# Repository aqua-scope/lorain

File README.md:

<h1> Lora Rain Sensor </h1>

<p>Lorain is an affordable LoraWAN rain sensor utilizing the RAK 3172 Lora Module that can be programmed using Arduino environment. </p>

<h2> Hardware</h2>

<p>There are multiple ways to acquire the hardware for the LoRain. The Aqua-Scope Webshop at <a href="https://shop.aqua-scope.com">shop.aqua-scope.com</a> offers different options depending on your willingness to spent own effort in exchange for money:
<ul>
<li>Complete product tested and ready to use</li>
<li>Kit with all needed components and need to solder some of the components and flash the firmware. 
The kit includes a PCBA almost fully populated</li>
<li>The plain enclosure of the device. You need to order the PCB / <a href="img/lorain_pcba.jpg">PCBA</a>, purchase and solder all components and flash the firmware. The 'How-To' below assumes this option.</li>
</ul>
<p> The folder /hardware contains the gerber data and Bill of material of the PCBs. You can order the PCB from one of the usual suspects for fast and cheap PCB manufacturing like jlcpcb or pcbway. Ordering own PCB and soldering all components requires a certain level of hardware knowledge and soldering skills. Hence, we don’t provide additional guidance beside offering the files for the PCB.
</p>

<h2>How to complete the LoRain Kit</h2>

<p>The LoRain Kit consists of the following components (see <a href="img/lorain_kit.png">image</a>):
<ul>
<li>enclosure including screws for mounting the enclosure to a flat surface, PCBA compartment and battery compartment</li>
<li>one screw to hold the battery compartment</li>
<li>2 * AA Batteries</li>
<li>CBA SMD complete</li>
<li>1 * 8.6 mm whip antenna</li>
<li>2 * wires to connect PCBA with battery compartment</li>
<li>Button</li>
<li>Reed contact</li>
</uL>
<p>The PCBA needs some soldering as shown in this (<a href="img/lorain_pcb_solder.png">image</a>). Please note that all soldering are done on the B-Sie that does not have any components. No soldering needed on A side with the components.
</p>
<ul>
<li>Connect the Battery + contact if the PCBA to the battery + contact of the battery compartment using the red wires</li>
<li>Connect the Battery - contact if the PCBA to the battery contact of the battery compartment using the black wires (<a href="img/lorain_pcb_solder.png">image</a>)</li>
<li>Insert the button into the hole of the PCB and solder it on the four pins</li>
<li>Solder the reed contact on the B-side as shown on the silk screen (<a href="img/lorain_pcb_back.png">image</a>)</li>
<li>Solder the whip antenna to the antenna tru-hole</li>
</ul> 

<h2> Firmware </h2>
  
<p>The firmware is written as Arduino Sketch using the RAK Wireless Arduino Environment. You need to install the Arduino IDE and follow the instructions of <a href="https://docs.rakwireless.com/Product-Categories/WisDuo/RAK3172-Module/Quickstart/#rak3172-as-a-stand-alone-device-using-rui3"> RAK wireless </a> to install the RAK board support package. </p>
  
<p>To flash a new firmware you need a simple USB-TTL-UART connector (<a href="https://www.amazon.de/AZDelivery-Konverter-kompatibel-Arduino-inklusive/dp/B089QJZ51Z/ref=asc_df_B089QJZ51Z"> e.g. this </a>). The firmware update mode on the RAK module is enabled using the AT command 'AT+BOOT' on the serial console of the Arduino IDE. </p>

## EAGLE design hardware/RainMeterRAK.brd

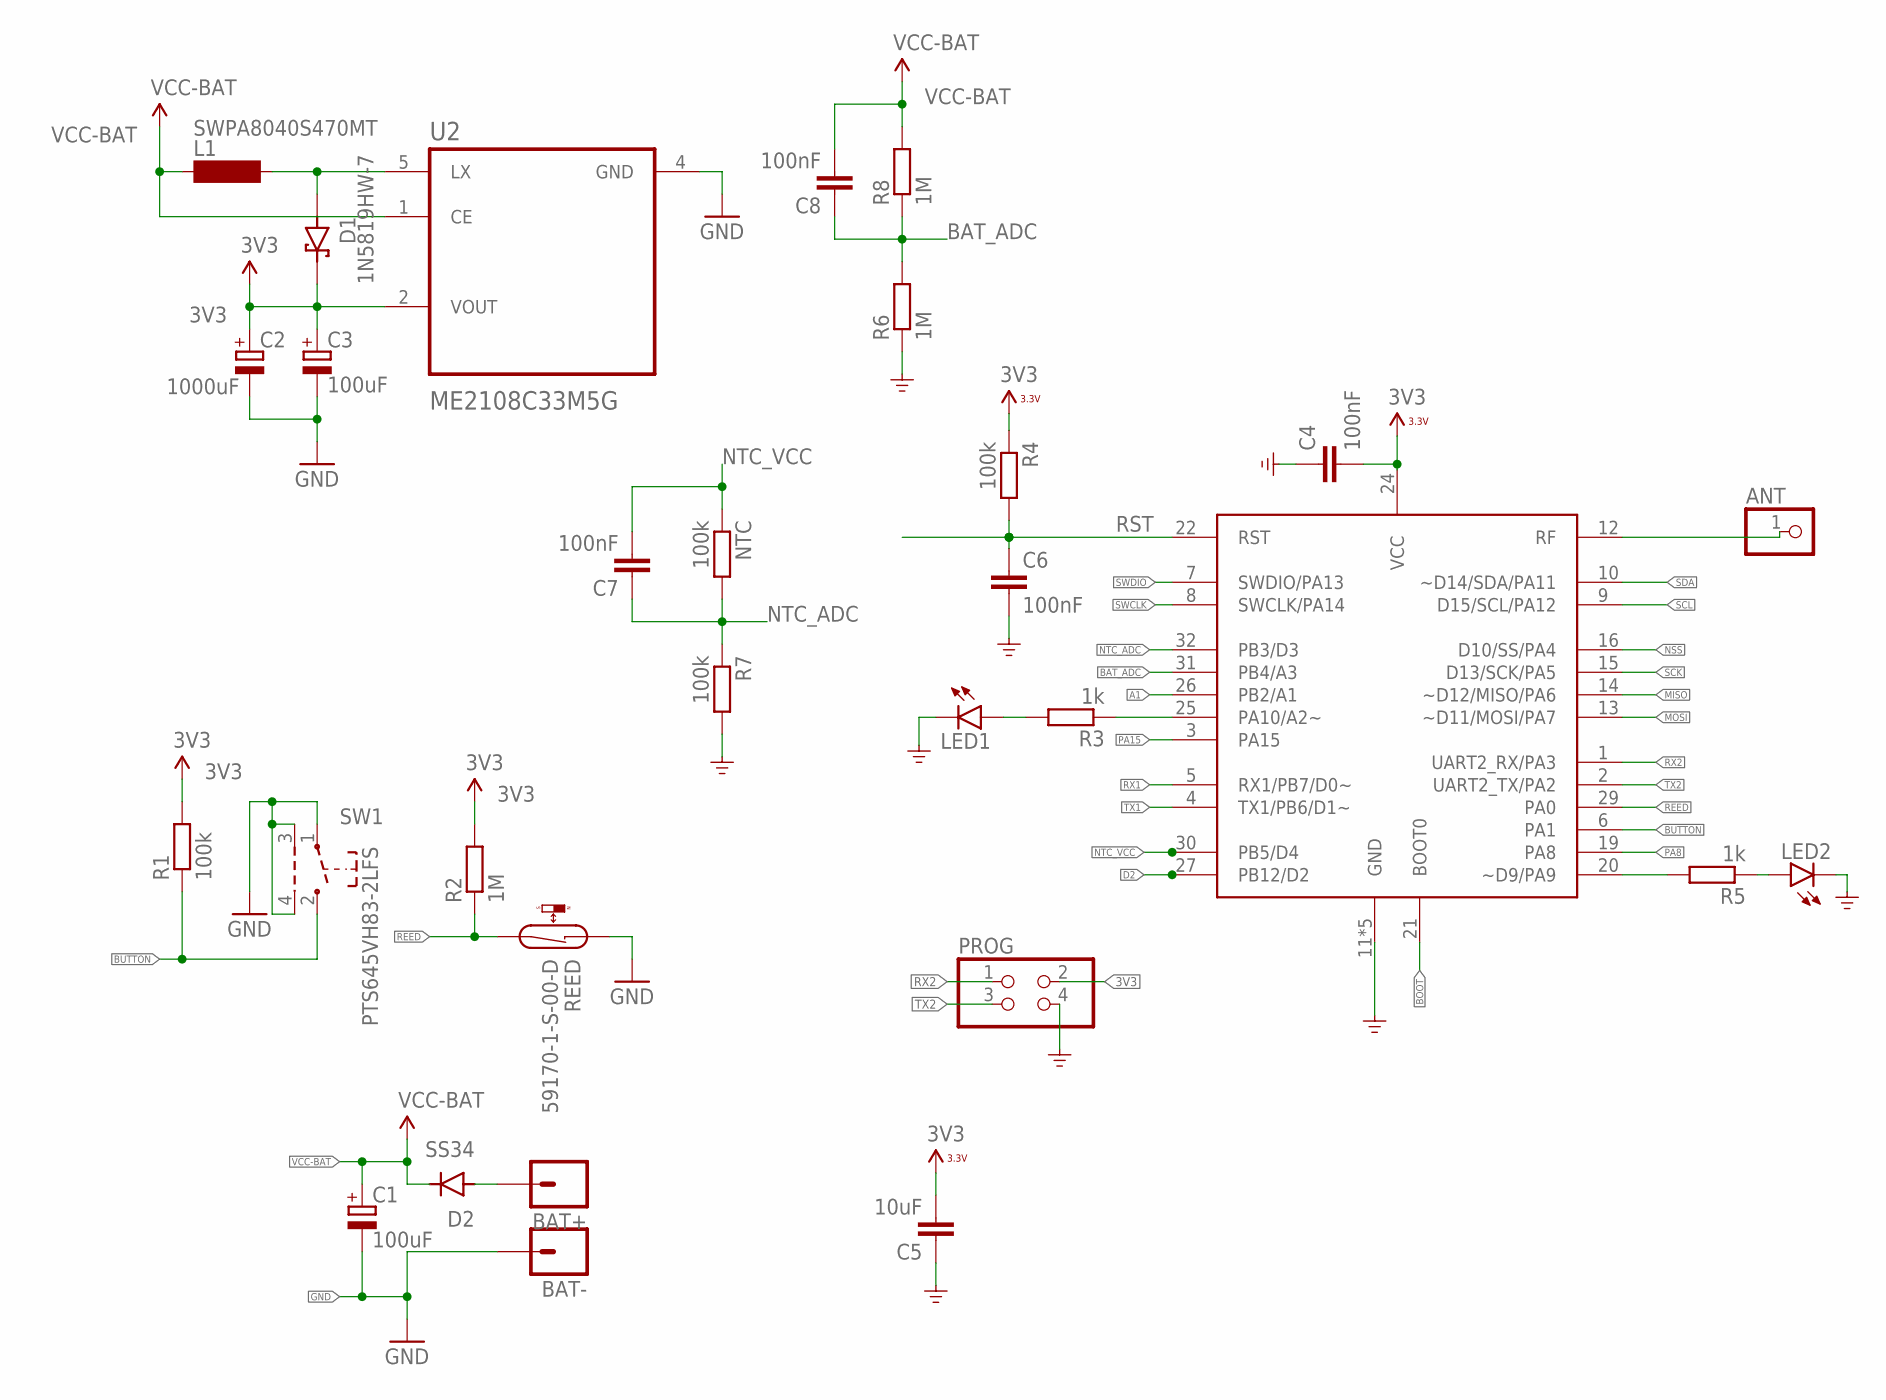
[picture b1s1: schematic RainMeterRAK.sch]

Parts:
ANT: PINHD-1X1; 1X01
BAT+: M01OFFSET; 1X01_OFFSET
BAT-: M01OFFSET; 1X01_OFFSET
C1, C3: 100uF; CT3528
C2: 1000uF; 140CLH-0810
C4, C6, C7, C8: 100nF; C0603
C5: 10uF; C0603
D1: 1N5819HW-7; SOD3715X145N
D2: SS34; SOD-123_MINI-SMA
L1: SWPA8040S470MT; SWPA8040S
LED1, LED2: LEDCHIP-LED0603; CHIP-LED0603
NTC: 100k; R0603
PROG: PINHD-2X2; 2X02
R1, R4, R7: 100k; R0603
R2, R6, R8: 1M; R0603
R3, R5: 1k; R0603
REED: 59170-1-S-00-D; CT10-G1
SW1: PTS645VH83-2LFS; SW_TACT_STANDARD_RIGHT_ANGLE
U1: RAK3172HF; RAK3172
U2: ME2108C33M5G; SOT23-5

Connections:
3V3: C2.+, C3.+, C4.2, C5.2, D1.C (K), PROG.2, R1.2, R2.2, R4.1, U1.24 (VCC), U2.2 (VOUT)
A1: U1.26 (PB2/A1)
BAT_ADC: C8.1, R6.2, R8.1, U1.31 (PB4/A3)
BOOT: U1.21 (BOOT0)
BUTTON: R1.1, SW1.2, U1.6 (PA1)
D2: U1.27 (PB12/D2)
GND: BAT-.1, C1.-, C2.-, C3.-, C4.1, C5.1, C6.2, LED1.C, LED2.C, PROG.4, R6.1, R7.2, REED.1, SW1.1, SW1.3, SW1.4, U1.11 (GND), U1.17 (GND), U1.18 (GND), U1.23 (GND), U1.28 (GND), U2.4 (GND)
MISO: U1.14 (~D12/MISO/PA6)
MOSI: U1.13 (~D11/MOSI/PA7)
unnamed: D1.A, L1.2, U2.5 (LX)
unnamed: R5.2, U1.20 (~D9/PA9)
unnamed: LED2.A, R5.1
unnamed: R3.1, U1.25 (PA10/A2~)
unnamed: LED1.A, R3.2
unnamed: ANT.1, U1.12 (RF)
unnamed: BAT+.1, D2.A
NSS: U1.16 (D10/SS/PA4)
NTC_ADC: C7.1, NTC.2, R7.1, U1.32 (PB3/D3)
NTC_VCC: C7.2, NTC.1, U1.30 (PB5/D4)
PA8: U1.19 (PA8)
PA15: U1.3 (PA15)
REED: R2.1, REED.2, U1.29 (PA0)
RST: C6.1, R4.2, U1.22 (RST)
RX1: U1.5 (RX1/PB7/D0~)
RX2: PROG.1, U1.1 (UART2_RX/PA3)
SCK: U1.15 (D13/SCK/PA5)
SCL: U1.9 (D15/SCL/PA12)
SDA: U1.10 (~D14/SDA/PA11)
SWCLK: U1.8 (SWCLK/PA14)
SWDIO: U1.7 (SWDIO/PA13)
TX1: U1.4 (TX1/PB6/D1~)
TX2: PROG.3, U1.2 (UART2_TX/PA2)
VCC-BAT: C1.+, C8.2, D2.C, L1.1, R8.2, U2.1 (CE)

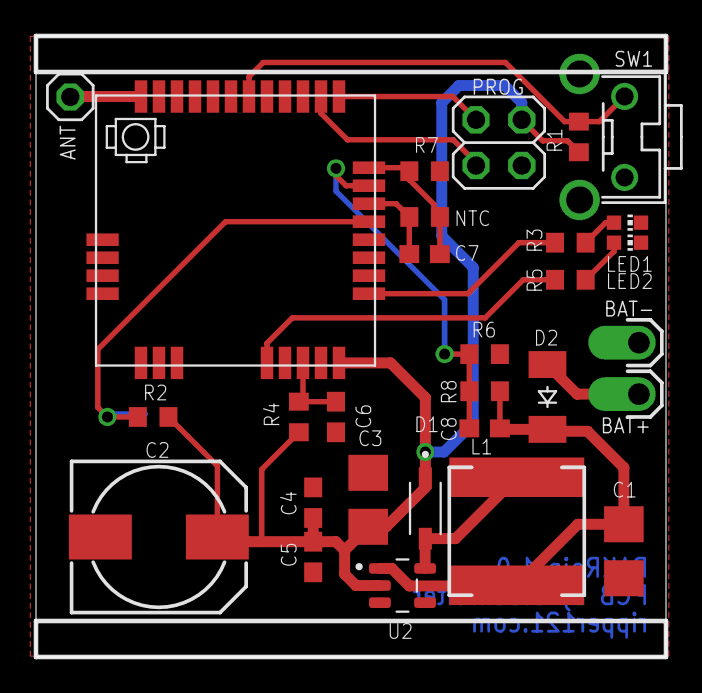
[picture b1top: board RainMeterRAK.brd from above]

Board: 2 copper layers, 35.0 x 34.5 mm, 30 parts (1 on the bottom side), 18 nets.

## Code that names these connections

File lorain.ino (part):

#define PIN_REED    0x00
#define PIN_BUTTON  0x01
#define PIN_LEDR    0x0A
#define PIN_LEDG    0x09
#define PIN_NTC     PB3
#define PIN_NTC_VCC PB5
#define PIN_VOLTAGE PB4

#define LED_ON  HIGH
#define LED_OFF LOW
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  Serial.printf("RAK Firmware Version: %s\r\n", api.system.firmwareVersion.get().c_str());
  pinMode(PIN_LEDG, OUTPUT);
  pinMode(PIN_LEDR, OUTPUT);
  pinMode(PIN_NTC_VCC, OUTPUT); 
  pinMode(PIN_NTC, INPUT);  
  pinMode(PIN_BUTTON, INPUT);  
  pinMode(PIN_VOLTAGE, INPUT);    
  pinMode(PIN_REED, INPUT);
  //analogReference(RAK_ADC_MODE_3_0);   
  if (api.lorawan.nwm.get()) { // LoRaWAN Mode
    digitalWrite(PIN_LEDG, LED_ON);
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  delay(3000); // emergency stop to input boot mode command
  readConfigFlash(); 
  loraSetup();
  attachInterrupt(PIN_REED, flip, FALLING);
  attachInterrupt(PIN_BUTTON, buttonpress, BUTTON_ON);  
  uAs = 1230; // *0.1 mAs setup 1,3 s @95 mA
}

void loop() {
  uint32_t diff = millis()/1000 - lastFlip;
  Serial.printf("Wakeup: time=%d flips=%d, count=%d,last=%d reed %d\n",millis()/1000,flipCount,heartbeat,lastFlip,digitalRead(PIN_REED));
  digitalWrite(PIN_NTC_VCC, HIGH); 
  delay(200);
  float r_ntc = (float)(configs[5] * 1000) * (1023.0/((float)analogRead(PIN_NTC))-1.0); // R7 is 100 kOhm    
  temperature  = (1 / ((log(r_ntc / 100000.0) / 4485.0) + (1.0 / (25.0 + 273.15))))- 273.15; 
  // NTCG164KF104FT1: b=4485/ r=100KOhm @ 25 Degree  
  voltage = analogRead(PIN_VOLTAGE)/10*75/100;
  digitalWrite(PIN_NTC_VCC, LOW);    
  uAs += configs[4] * 6/100; // * 0,1 mAs;
  if (++heartbeat >= configs[2] || flipCount || (heavyRain && diff > configs[3])) {
    confirmcount ++;
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
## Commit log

2022-10-03 Initial Upload
2022-10-03 Initial Readme
2022-10-03 File Upload
2022-11-30 Update rain_ttn_decoder.js
    display some values as float, fix 2-complement display on temperature value, config values now in config array
2023-07-11 add EUPL license

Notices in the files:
parts and their libraries:
SparkFun-Connectors: Licensing: Creative Commons ShareAlike 4.0 International - https://creativecommons.org/licenses/by-sa/4.0
PatternAgents-Beautify: License : http://creativecommons.org/licenses/by-sa/3.0
(Creative Commons 3.0)
